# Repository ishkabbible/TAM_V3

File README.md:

# Triple_Attenuverter_Mixer_v3

The TAM is three precision attenuators/attenuverters feeding into a 3-input, non-inverting mixer. The attenuXer sections are fully independent, and the output jacks are normalled to the mixer. Each section has 2 jumpers: one to select attenuator (gain = [0, +1]) or attenuverter (gain = [-1, +1]) operation. The other selects whether the input is normalled to +5V.

Additionally, this repository contains 2 different panel designs, the 3U x 6hp vertical panel, and a 1U x 20hp "tile" design. You will want to add knobs to the 1U build, since the pointer on the pots will be pointing sideways. The panel designs are identical to V2 and have not been updated.

LICENSE: The more I read about open source hardware licensing, the more confused I become. Apparently there is no real legal framework for it. That said, everyone seems to be doing it, so I'll join the crowd and hope the law eventually catches up with the people.
There is nothing unique or clever in this design, just the one op-amp attenuverter that everyone uses, and a non-inverting summer. I expect there are a dozen modules out there that have nearly the identical schematic. 
So I am releasing this design under the CC-BY-SA license. Feel free to contact me at ishkabbible at gmail.com if you feel I should be crediting you for any part of the design.

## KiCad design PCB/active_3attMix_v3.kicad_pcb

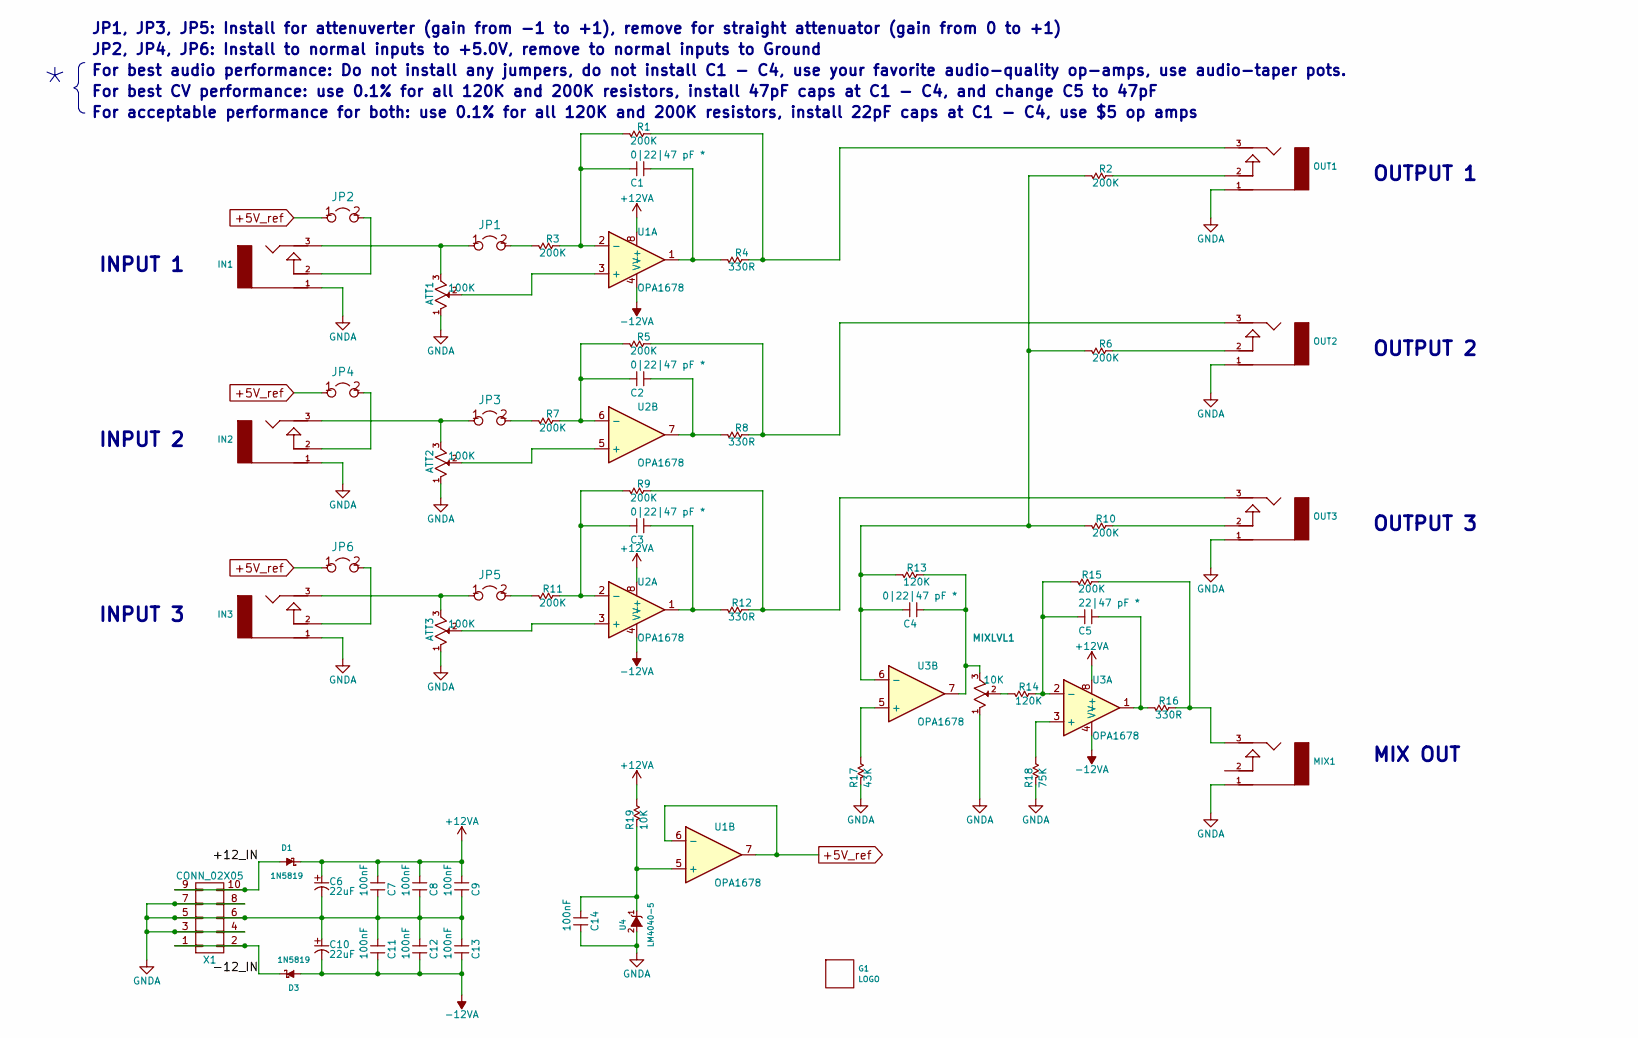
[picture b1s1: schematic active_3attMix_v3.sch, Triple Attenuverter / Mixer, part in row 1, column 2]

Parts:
ATT1, ATT2, ATT3: 100K; POT_SONG_HUEI_9mm_tall_trimmer
C1, C2, C3, C4: 0|22|47 pF *; C_0805_DKH
C5: 22|47 pF *; C_0805_DKH
C6, C10: 22uF; CP_Elec_5x5.8
C7, C8, C9, C11, C12, C13, C14: 100nF; C_0805_DKH
D1, D3: 1N5819; D_SOD-123
G1: LOGO; Hamara_labs_4_tiny
IN1, IN2, IN3: AUDIO-JACK-PJ301M-12; PJ301M-12_veils_sharedGround
JP1, JP2, JP3, JP4, JP5, JP6: header-2P; jump-2P
MIX1: AUDIO-JACK-PJ301M-12; PJ301M-12_veils_sharedGround
MIXLVL1: 10K; POT_SONG_HUEI_9mm_tall_trimmer
OUT1, OUT2, OUT3: AUDIO-JACK-PJ301M-12; PJ301M-12_veils_sharedGround
R1, R2, R3, R5, R6, R7, R9, R10, R11, R15: 200K; R_0805_DKH_hand
R4, R8, R12, R16: 330R; R_0805_DKH_hand
R13, R14: 120K; R_0805_DKH_hand
R17: 43K; R_0805_DKH_hand
R18: 75K; R_0805_DKH_hand
R19: 10K; R_0805_DKH_hand
U1, U2, U3: OPA1678; SOIC-8_3.9x4.9mm_Pitch1.27mm
U4: LM4040-5; SOT-23_Handsoldering
X1: CONN_02X05; HEADER_2.54_2x5

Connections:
+5V_ref: JP2.1, JP4.1, JP6.1, U1.6 (-), U1.7
+12VA: C6.1, C7.1, C8.1, C9.1, D1.1 (K), R19.2, U1.8 (V+), U2.8 (V+), U3.8 (V+)
-12VA: C10.2, C11.2, C12.2, C13.2, D3.2 (A), U1.4 (V-), U2.4 (V-), U3.4 (V-)
/+12_IN: D1.2 (A), X1.9, X1.10
/-12_IN: D3.1 (K), X1.1, X1.2
GNDA: ATT1.1, ATT2.1, ATT3.1, C6.2, C7.2, C8.2, C9.2, C10.1, C11.1, C12.1, C13.1, C14.2, IN1.1 (RING), IN2.1 (RING), IN3.1 (RING), MIX1.1 (RING), MIXLVL1.1, OUT1.1 (RING), OUT2.1 (RING), OUT3.1 (RING), R17.1, R18.1, U4.2 (A), X1.3, X1.4, X1.5, X1.6, X1.7, X1.8
unnamed: ATT1.2, U1.3 (+)
unnamed: ATT1.3, IN1.3 (TIP), JP1.1
unnamed: ATT2.2, U2.5 (+)
unnamed: ATT2.3, IN2.3 (TIP), JP3.1
unnamed: ATT3.2, U2.3 (+)
unnamed: ATT3.3, IN3.3 (TIP), JP5.1
unnamed: C1.1, R4.2, U1.1
unnamed: C1.2, R1.2, R3.1, U1.2 (-)
unnamed: C2.1, R8.2, U2.7
unnamed: C2.2, R5.2, R7.1, U2.6 (-)
unnamed: C3.1, R12.2, U2.1
unnamed: C3.2, R9.2, R11.1, U2.2 (-)
unnamed: C4.1, MIXLVL1.3, R13.1, U3.7
unnamed: C4.2, R2.2, R6.2, R10.2, R13.2, U3.6 (-)
unnamed: C5.1, R16.2, U3.1
unnamed: C5.2, R14.1, R15.2, U3.2 (-)
unnamed: C14.1, R19.1, U1.5 (+), U4.1 (K)
unnamed: IN1.2 (NORM), JP2.2
unnamed: IN2.2 (NORM), JP4.2
unnamed: IN3.2 (NORM), JP6.2
unnamed: JP1.2, R3.2
unnamed: JP3.2, R7.2
unnamed: JP5.2, R11.2
unnamed: MIX1.3 (TIP), R15.1, R16.1
unnamed: MIXLVL1.2, R14.2
unnamed: OUT1.2 (NORM), R2.1
unnamed: OUT1.3 (TIP), R1.1, R4.1
unnamed: OUT2.2 (NORM), R6.1
unnamed: OUT2.3 (TIP), R5.1, R8.1
unnamed: OUT3.2 (NORM), R10.1
unnamed: OUT3.3 (TIP), R9.1, R12.1
unnamed: R17.2, U3.5 (+)
unnamed: R18.2, U3.3 (+)

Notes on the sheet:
INPUT 1
INPUT 2
INPUT 3
OUTPUT 1
OUTPUT 2
OUTPUT 3
MIX OUT
JP1, JP3, JP5: Install for attenuverter (gain from -1 to +1), remove for straight attenuator (gain from 0 to +1)
JP2, JP4, JP6: Install to normal inputs to +5.0V, remove to normal inputs to Ground
For best audio performance: Do not install any jumpers, do not install C1 - C4, use your favorite audio-quality op-amps, use audio-taper pots.
For best CV performance: use 0.1% for all 120K and 200K resistors, install 47pF caps at C1 - C4, and change C5 to 47pF
For acceptable performance for both: use 0.1% for all 120K and 200K resistors, install 22pF caps at C1 - C4, use $5 op amps

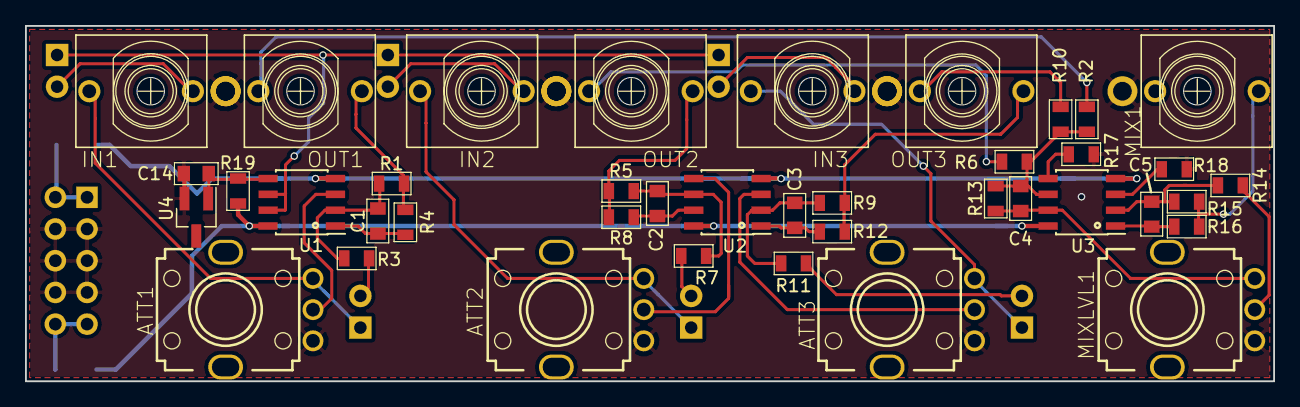
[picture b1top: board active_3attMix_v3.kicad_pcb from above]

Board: 2 copper layers, 100.0 x 28.5 mm, 58 parts (0 on the bottom side), 39 nets.

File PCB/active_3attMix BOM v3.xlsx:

|  |  |  |  | NOTE: Prices are for rough planning only, they change on a daily basis
Quantity | Designator | Designation | Package | Vendor |  | each | ext. | Notes |  |  | pads
2 | C6,C10 | 22uF | CP_Elec_5x5.8 | Mouser | 667-EEE-FK1E220R | 0.41 | 0.82
1 | U4 | LM4040C50FTA | LM4040-5 | Mouser | 522-LM4040C50FTA | 0.64 | 0.64 | Use LM4040A for more accurate 5V normaled to the inputs |  |  | 3 | 3
3 | U1,U2,U3 | OPA1678IDR | SOIC-8_3.9x4.9mm_Pitch1.27mm | Mouser | 595-OPA1678IDR | 0.83 | 2.4899999999999998 | TL072 is cheaper if you don't care about performance |  |  | 8 | 24
2 | D3,D1 | 1N5819HW-7-F | D_SOD-123 | Mouser | 621-1N5819HW-F | 0.44 | 0.88 |  |  |  | 2 | 4
1 | X1 | Header 2 x 5, 0.1" | HEADER_2.54_2x5 |  | 538-10-89-7101 | 0.56999999999999995 | 0.56999999999999995 | Available cheaper elsewhere |  |  |  | 0
6 | JP6,JP5,JP4,JP3,JP2,JP1 | header-2P, 0.1" | jump-2P |  | 571-826936-2 | 0.1 | 0.60000000000000009 | Available cheaper elsewhere |  |  |  | 0
7 | IN1,IN2,IN3,MIX1,OUT1,OUT2,OUT3 | PJ301M-12 / PJ398SM Jack | PJ301M-12_shared_ground | Thonk | https://www.thonk.co.uk/shop/3-5mm-jacks/ | 0.53 | 3.71 | must buy nuts separately. PJ398SM is upgraded part |  |  |  | 0
3 | ATT1,ATT2,ATT3 | 100K | POT_SONG_HUEI_9mm_tall_trimmer | Thonk | https://www.thonk.co.uk/shop/ttpots/ | 1.1100000000000001 | 3.33 | Linear for CV math, Audio for audio mixer |  |  |  | 0
1 | MIXLVL1 | 10K | POT_SONG_HUEI_9mm_tall_trimmer | Thonk | https://www.thonk.co.uk/shop/ttpots/ | 1.1100000000000001 | 1.1100000000000001 | Linear for CV math, Audio for audio mixer |  |  |  | 0
5 | C1,C2,C3,C4,C5 | 10pF | C_0805_DKH | Mouser | 77-VJ0805A100GXAPBC | 0.1 | 0.5 |  |  |  | 2 | 10
7 | C7,C8,C9,C11,C12,C13,C14 | 100nF | C_0805_DKH | Mouser | 581-08055C104KAT4A | 0.1 | 0.70000000000000007 |  |  |  | 2 | 14
10 | R1,R2,R3,R5,R6,R7,R9,R10,R11,R15 | 200K, 0.1% | R_0805_DKH | Mouser | 603-AT0805BRD07200KL | 0.26100000000000001 | 2.6100000000000003 |  |  |  | 2 | 20
4 | R4,R8,R12,R16 | 330R | R_0805_DKH | Mouser | 603-RC0805FR-07330RL | 1.6E-2 | 6.4000000000000001E-2 | buy 10 |  |  | 2 | 8
2 | R13,R14 | 120K, 0.1% | R_0805_DKH | Mouser | 603-RT0805BRD07120KL | 0.39 | 0.78 |  |  |  | 2 | 4
1 | R17 | 43K | R_0805_DKH | Mouser | 603-RC0805FR-0743KL | 0.1 | 0.1 |  |  |  | 2 | 2
1 | R18 | 75K | R_0805_DKH | Mouser | 603-RC0805FR-0775KL | 0.1 | 0.1 |  |  |  | 2 | 2
1 | R19 | 10K | R_0805_DKH | Mouser | 603-RC0805FR-0710KL | 0.1 | 0.1 |  |  |  | 2 | 2
6 | JP6,JP5,JP4,JP3,JP2,JP1 |  | 2-pin Jumpers | Mouser | 806-SX1100-B | 2.1999999999999999E-2 | 0.13200000000000001 | buy 25, available cheaper elsewhere
 |  |  |  |  |  | subtotal | 19.236000000000008
1 |  |  | PCB |  |  | 10 | 10
1 |  |  | Panel |  |  | 10 | 10
65 | total parts |  |  |  |  | total | 44.045000000000009
 |  |  |  |  | kit cost |  | 50
37 | SMTs + filter caps

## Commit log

2019-07-10 Initial upload

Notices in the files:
PCB/active_3attMix_v3.sch:
(C) 2019 D. Hamara
